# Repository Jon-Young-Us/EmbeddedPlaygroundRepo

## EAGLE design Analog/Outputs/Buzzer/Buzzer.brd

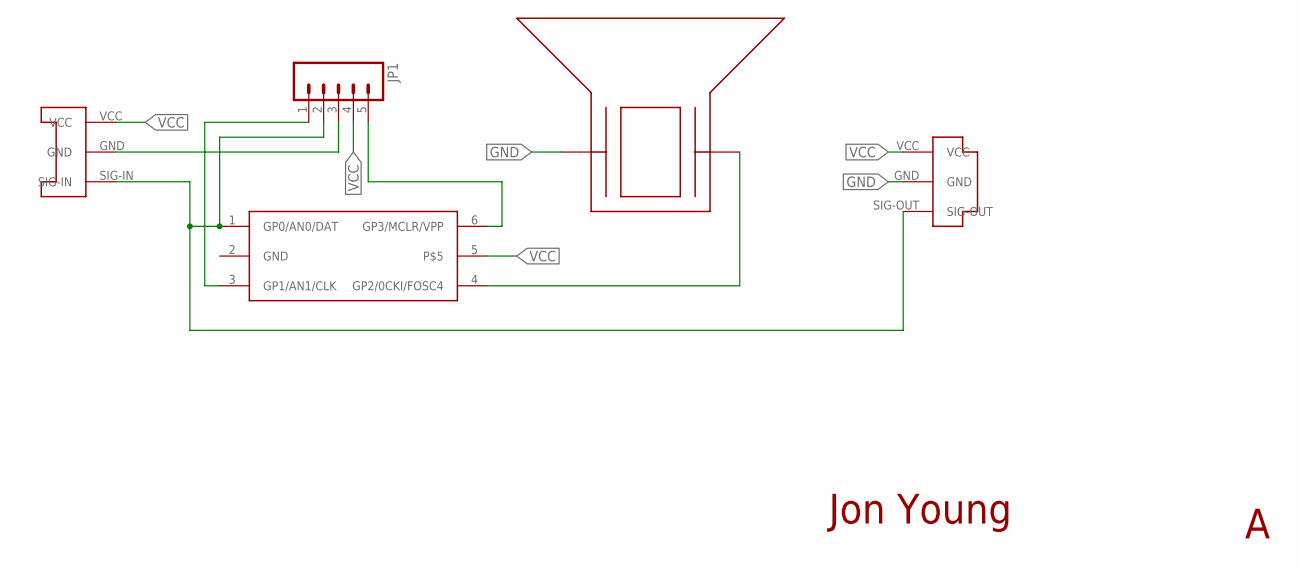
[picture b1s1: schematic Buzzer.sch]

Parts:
JP1: M051.27MM; 1X05-1.27MM
U$1: CONN-PLUG-3POS-3MM; PLUG-3POS-3MM-SMD
U$2: CONN-SOCKET-3POS-3MM; SOCKET-3POS-3MM-SMD
U$3: BUZZER; BUZZER-PKMCS0909E4000-R1
U$6: PIC10F2XXT-I/OT; SOT23-6

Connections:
GND: JP1.3, U$1.GND, U$2.GND, U$3.P$1, U$6.2 (GND)
unnamed: JP1.1, U$6.3 (GP1/AN1/CLK)
unnamed: JP1.2, U$1.SIG-OUT, U$2.SIG-IN, U$6.1 (GP0/AN0/DAT)
P$5: U$6.5
SIG-IN: U$3.P$2, U$6.4 (GP2/0CKI/FOSC4)
VCC: JP1.4, JP1.5, U$1.VCC, U$2.VCC, U$6.6 (GP3/MCLR/VPP)

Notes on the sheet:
Jon Young

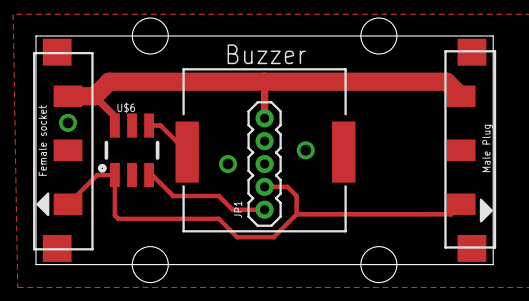
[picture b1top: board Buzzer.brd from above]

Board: 2 copper layers, 25.4 x 12.7 mm, 5 parts (0 on the bottom side), 5 nets.

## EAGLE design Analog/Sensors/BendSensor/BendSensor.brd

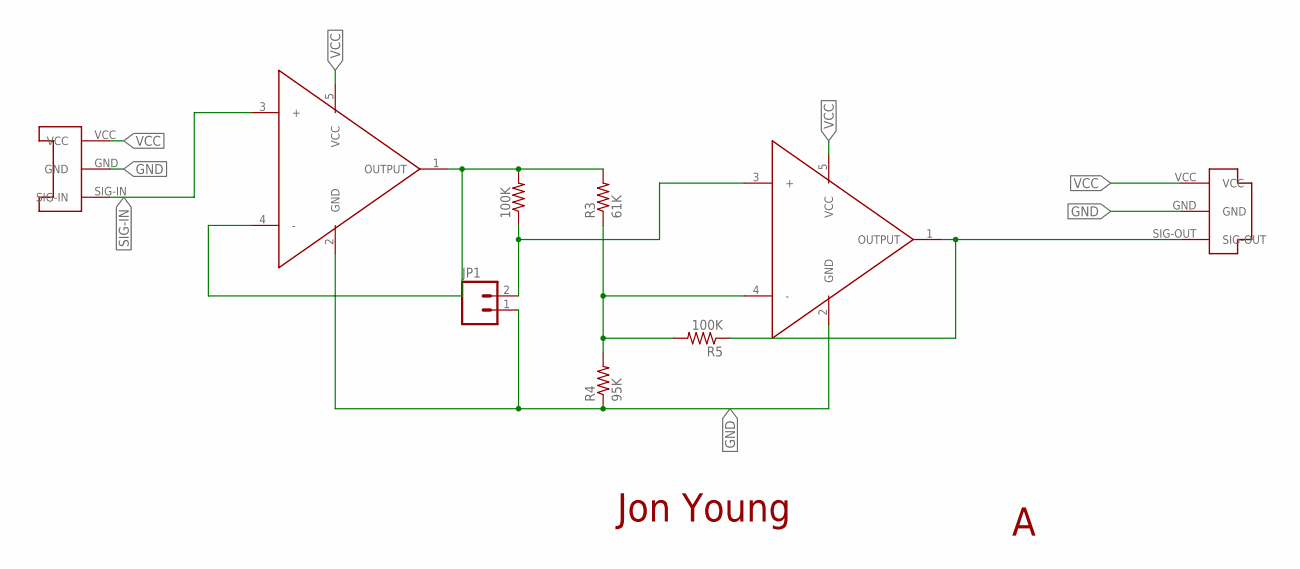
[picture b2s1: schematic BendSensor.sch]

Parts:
100K: RESISTOR0603; 0603-RES
JP1: M02PTH3; 1X02_LONGPADS
R3: 61K; 0603-RES
R4: 95K; 0603-RES
R5: 100K; 0603-RES
U$1: CONN-PLUG-3POS-3MM; PLUG-3POS-3MM-SMD
U$2: CONN-SOCKET-3POS-3MM; SOCKET-3POS-3MM-SMD
U$3, U$4: OPAMP-MCP6001SOT23-5; SOT23-5

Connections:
GND: JP1.1, R4.1, U$1.GND, U$2.GND, U$3.2 (GND), U$4.2 (GND)
unnamed: R5.1, U$1.SIG-OUT, U$4.1 (OUTPUT)
unnamed: R3.1, R4.2, R5.2, U$4.4 (-)
unnamed: 100K.2, R3.2, U$3.1 (OUTPUT), U$3.4 (-)
unnamed: 100K.1, JP1.2, U$4.3 (+)
SIG-IN: U$2.SIG-IN, U$3.3 (+)
VCC: U$1.VCC, U$2.VCC, U$3.5 (VCC), U$4.5 (VCC)

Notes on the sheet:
Jon Young

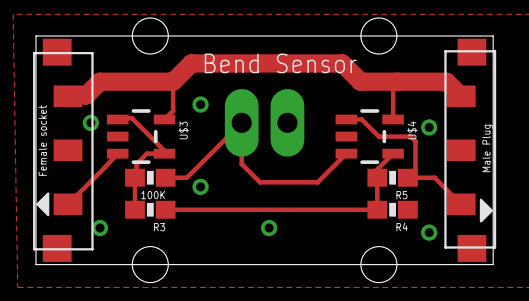
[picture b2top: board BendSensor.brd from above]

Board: 2 copper layers, 25.4 x 12.7 mm, 9 parts (0 on the bottom side), 7 nets.

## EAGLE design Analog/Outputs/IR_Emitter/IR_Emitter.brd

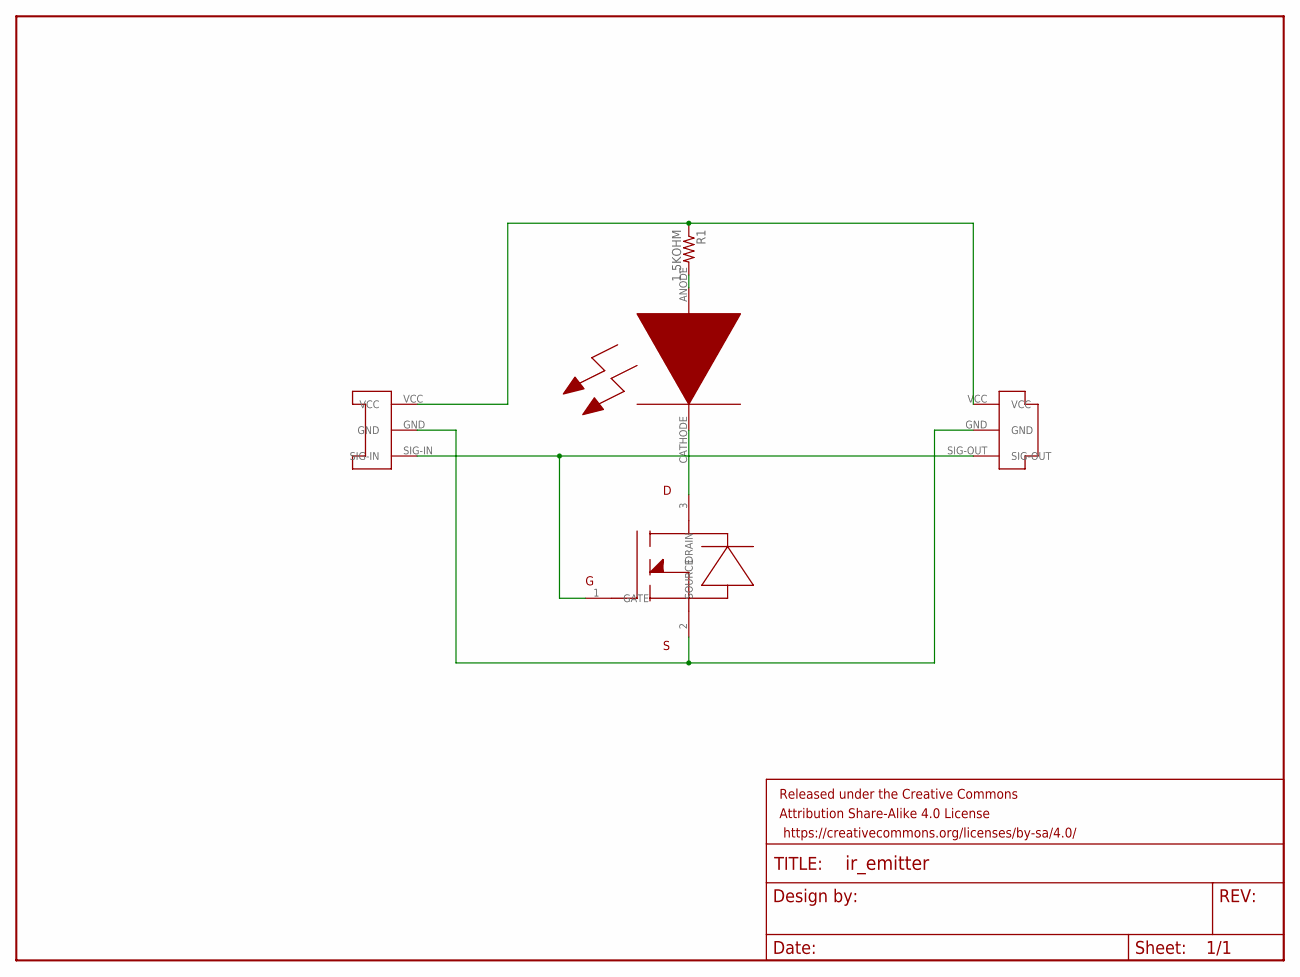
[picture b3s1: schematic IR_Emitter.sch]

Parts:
FRAME1: FRAME-LETTERNO_PACKAGE; DUMMY
R1: 1.5KOHM; 0603
U$1: CONN-PLUG-3POS-3MM; PLUG-3POS-3MM-SMD
U$2: CONN-SOCKET-3POS-3MM; SOCKET-3POS-3MM-SMD
U$3: MOSFET-N-CHAN; SOT23-3
U$4: IR-EMITTER-VSMB2943G; VEMD2020X01

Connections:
GND: U$1.GND, U$2.GND, U$3.2 (SOURCE)
unnamed: R1.2, U$4.ANODE
unnamed: U$3.3 (DRAIN), U$4.CATHODE
SIG: U$1.SIG-OUT, U$2.SIG-IN, U$3.1 (GATE)
VCC: R1.1, U$1.VCC, U$2.VCC

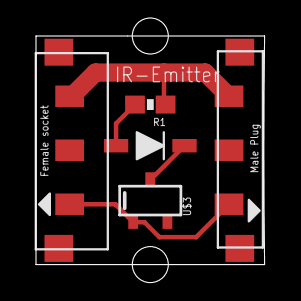
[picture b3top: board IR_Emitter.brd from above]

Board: 2 copper layers, 12.7 x 12.7 mm, 6 parts (0 on the bottom side), 5 nets.

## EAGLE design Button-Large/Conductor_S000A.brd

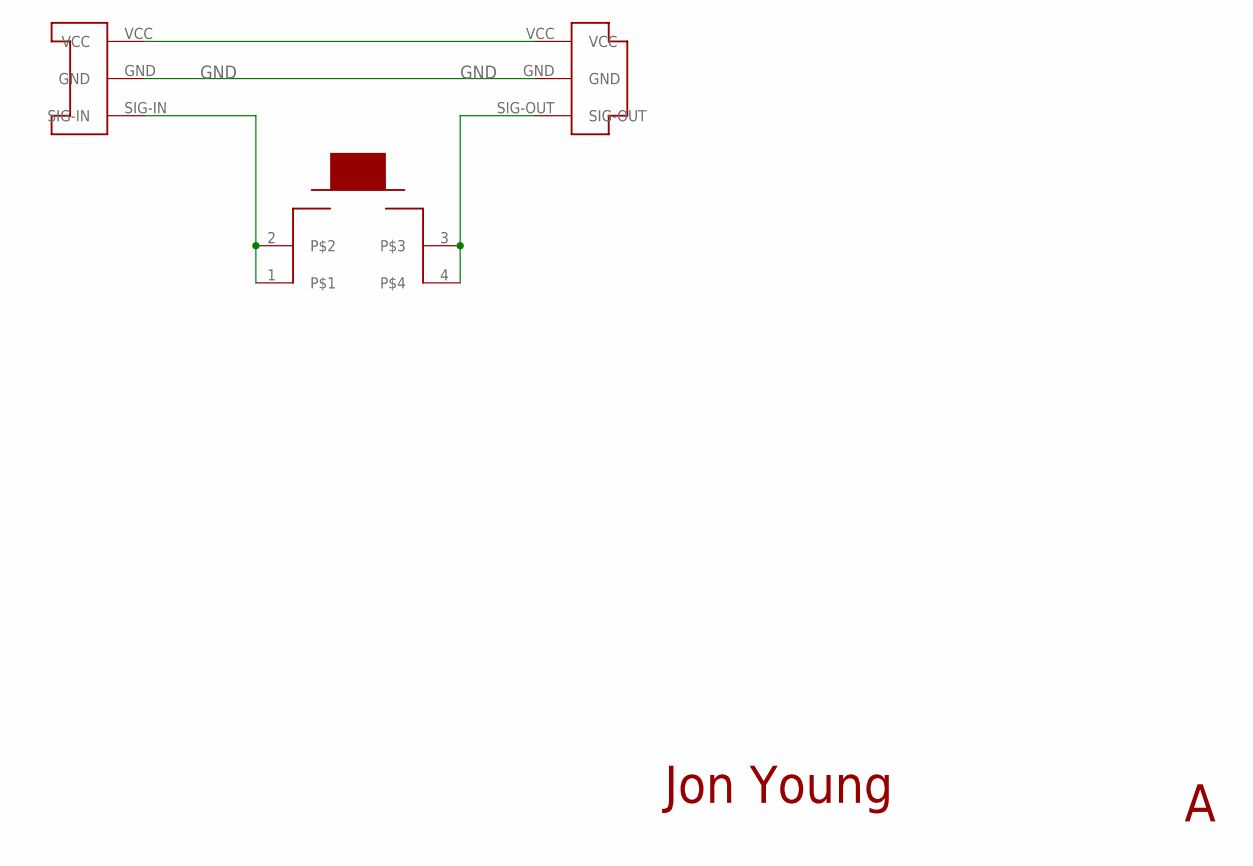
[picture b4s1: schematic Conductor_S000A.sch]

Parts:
U$1: CONN-PLUG-3POS-3MM; PLUG-3POS-3MM-SMD
U$2: CONN-SOCKET-3POS-3MM; SOCKET-3POS-3MM-SMD
U$3: PUSH_BUTTON; ESWITCH-TL3300CF260Q

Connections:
GND: U$1.GND, U$2.GND
unnamed: U$2.SIG-IN, U$3.1, U$3.2
unnamed: U$1.SIG-OUT, U$3.3, U$3.4
VCC: U$1.VCC, U$2.VCC

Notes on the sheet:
Jon Young

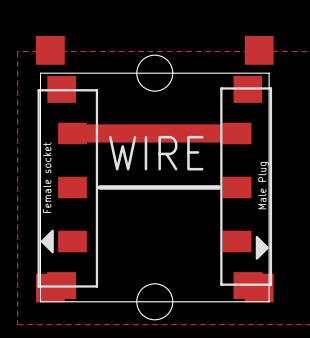
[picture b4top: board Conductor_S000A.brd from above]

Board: 2 copper layers, 12.7 x 12.7 mm, 3 parts (0 on the bottom side), 4 nets.

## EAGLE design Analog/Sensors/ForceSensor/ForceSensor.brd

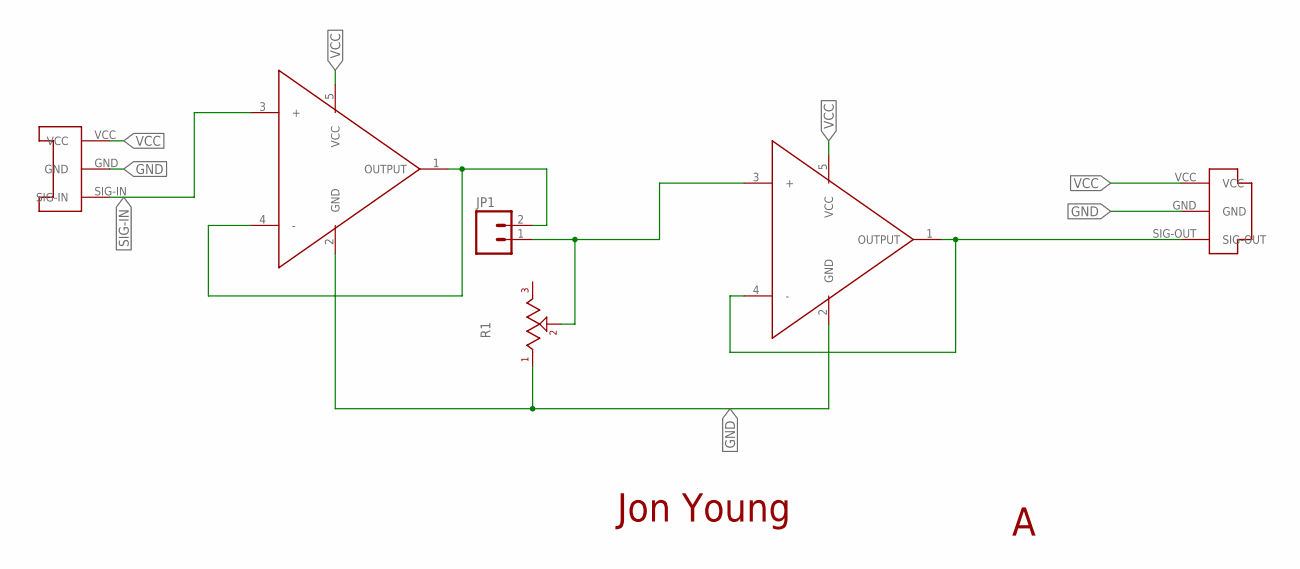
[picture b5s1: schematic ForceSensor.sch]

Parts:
JP1: M02PTH3; 1X02_LONGPADS
R1: POT-TRIM-SMD-BOURNS-3314J-1; POT-TRIM-SMD-BOURNS-3314
U$1: CONN-PLUG-3POS-3MM; PLUG-3POS-3MM-SMD
U$2: CONN-SOCKET-3POS-3MM; SOCKET-3POS-3MM-SMD
U$3, U$4: OPAMP-MCP6001SOT23-5; SOT23-5

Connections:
GND: R1.3 (1), U$1.GND, U$2.GND, U$3.2 (GND), U$4.2 (GND)
unnamed: U$1.SIG-OUT, U$4.1 (OUTPUT), U$4.4 (-)
unnamed: JP1.2, U$3.1 (OUTPUT), U$3.4 (-)
unnamed: JP1.1, R1.2, U$4.3 (+)
SIG-IN: U$2.SIG-IN, U$3.3 (+)
VCC: U$1.VCC, U$2.VCC, U$3.5 (VCC), U$4.5 (VCC)

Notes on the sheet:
Jon Young

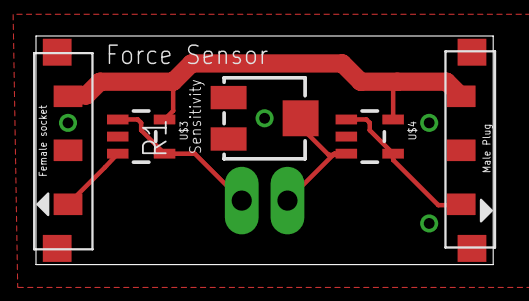
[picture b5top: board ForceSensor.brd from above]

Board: 2 copper layers, 25.4 x 12.7 mm, 6 parts (0 on the bottom side), 6 nets.

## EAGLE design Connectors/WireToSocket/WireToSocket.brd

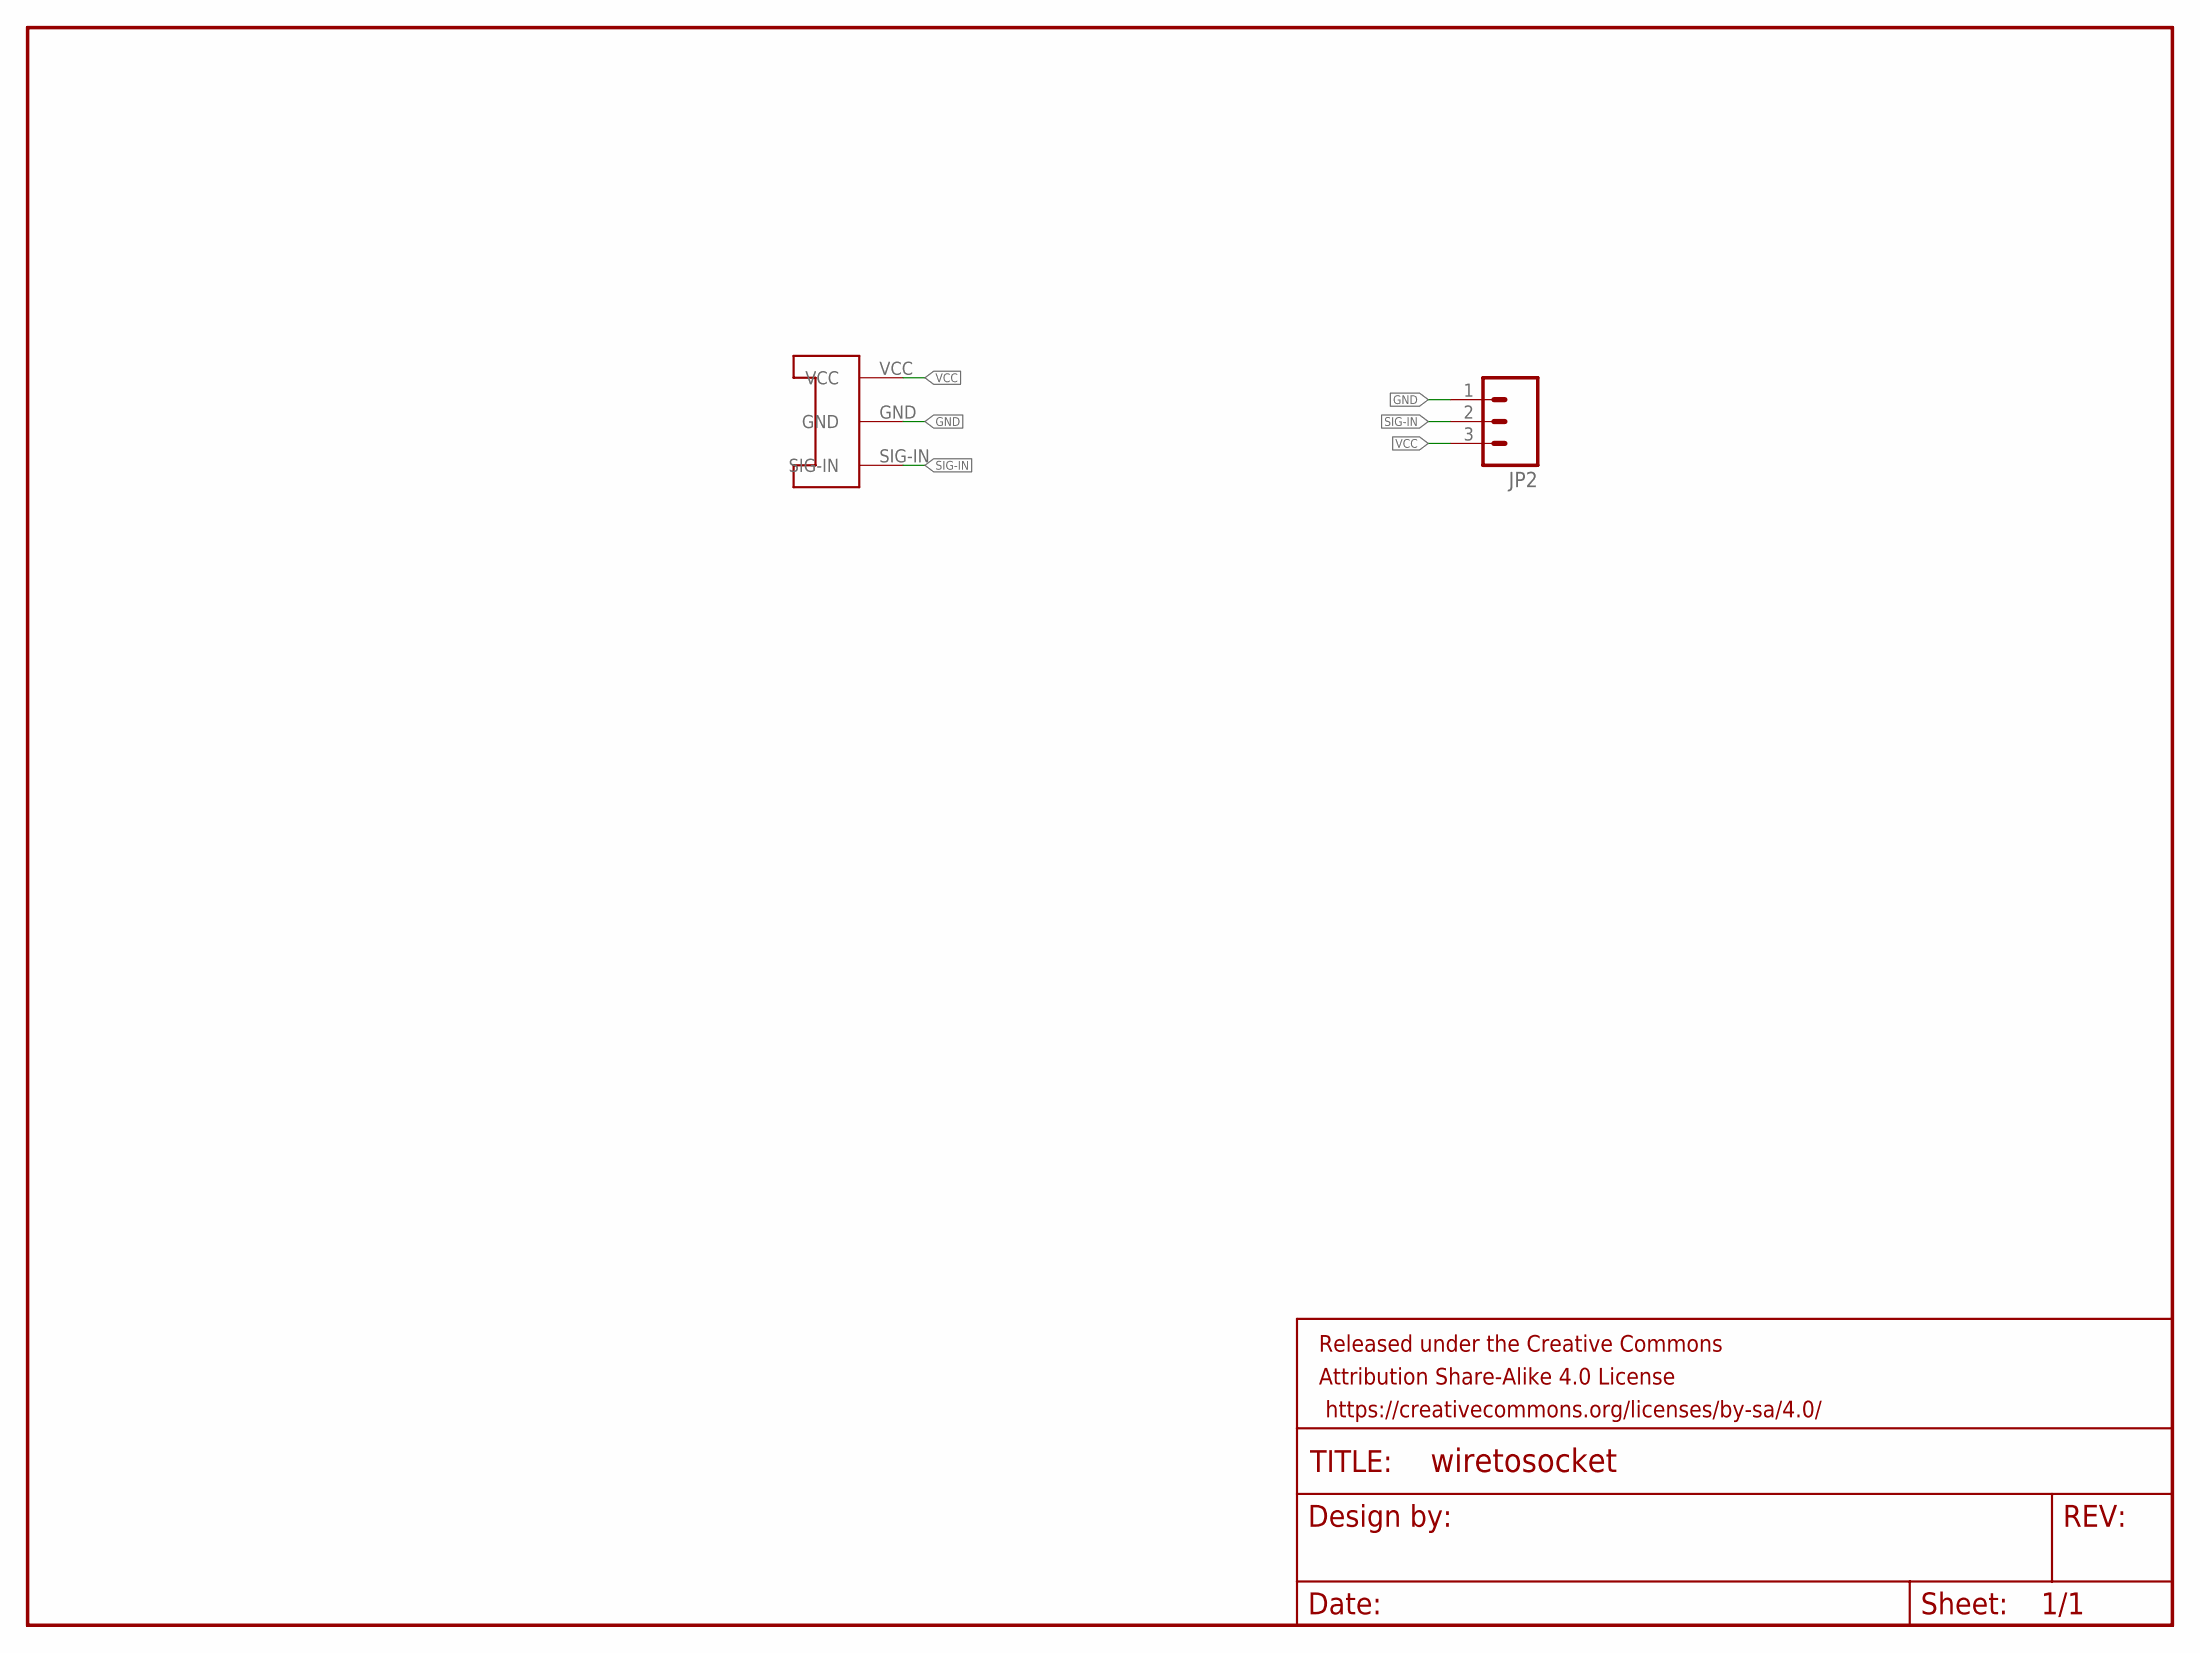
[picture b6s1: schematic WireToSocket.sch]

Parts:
FRAME1: FRAME-LETTERNO_PACKAGE; DUMMY
JP2: M03SMD; 1X03-1MM-RA
U$1: CONN-SOCKET-3POS-3MM; SOCKET-3POS-3MM-SMD

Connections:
GND: JP2.1, U$1.GND
SIG-IN: JP2.2, U$1.SIG-IN
VCC: JP2.3, U$1.VCC

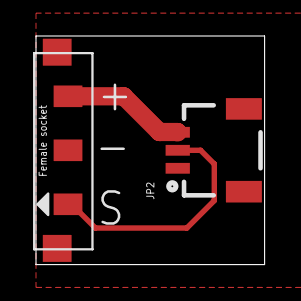
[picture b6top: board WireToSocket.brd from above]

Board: 2 copper layers, 12.7 x 12.7 mm, 3 parts (0 on the bottom side), 3 nets.

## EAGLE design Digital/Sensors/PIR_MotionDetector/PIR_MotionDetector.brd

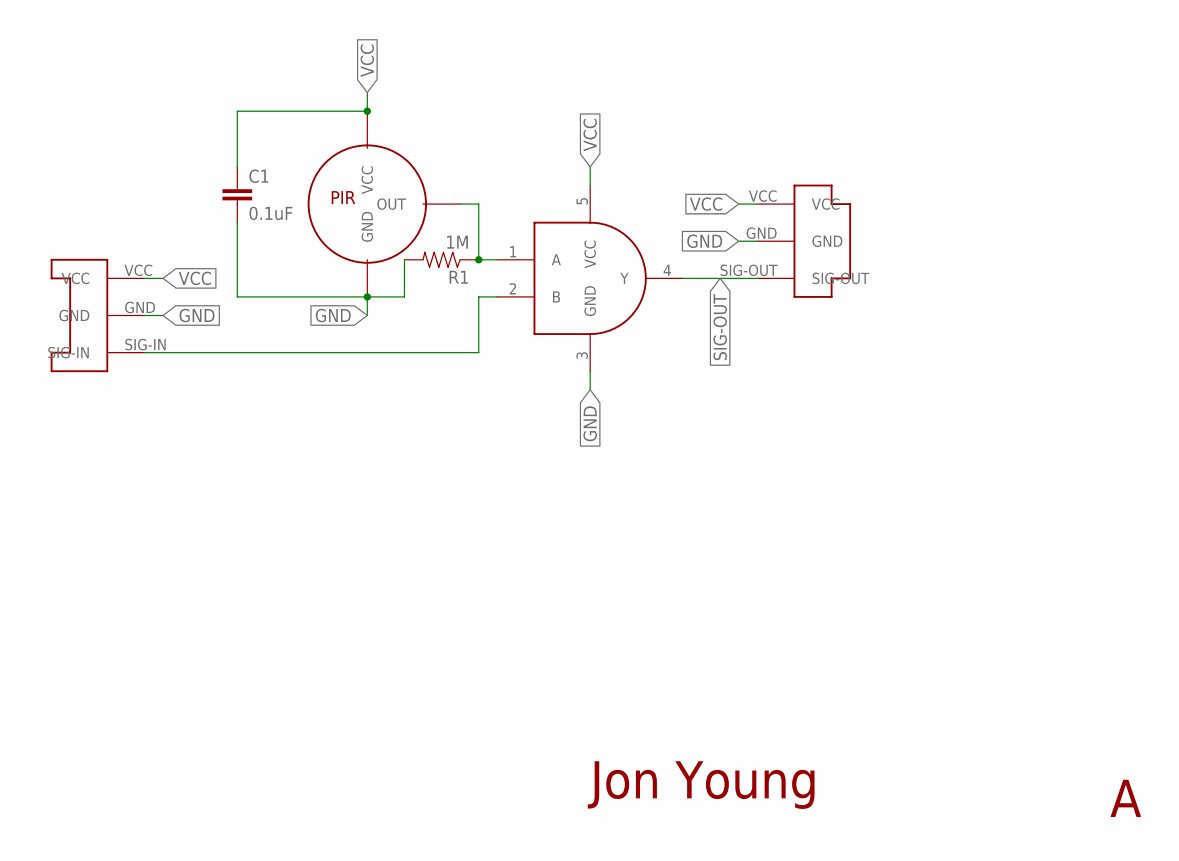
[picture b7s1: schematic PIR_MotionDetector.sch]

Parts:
C1: 0.1uF; 0603-CAP
R1: 1M; 0603-RES
U$1: CONN-PLUG-3POS-3MM; PLUG-3POS-3MM-SMD
U$2: CONN-SOCKET-3POS-3MM; SOCKET-3POS-3MM-SMD
U$3: PIR-PANASONIC-WL; TO-5-3PIN
U$4: AND-NC7SZ08; SC70

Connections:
GND: C1.2, R1.2, U$1.GND, U$2.GND, U$3.GND, U$4.3 (GND)
unnamed: R1.1, U$3.OUT, U$4.1 (A)
SIG-IN: U$2.SIG-IN, U$4.2 (B)
SIG-OUT: U$1.SIG-OUT, U$4.4 (Y)
VCC: C1.1, U$1.VCC, U$2.VCC, U$3.VCC, U$4.5 (VCC)

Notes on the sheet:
Jon Young

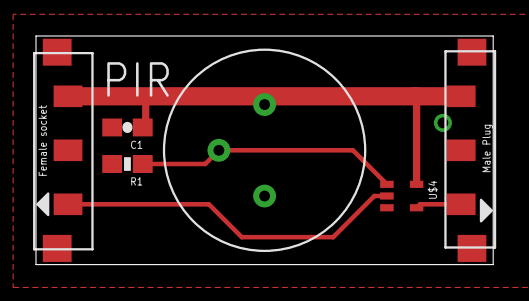
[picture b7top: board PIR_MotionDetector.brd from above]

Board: 2 copper layers, 25.4 x 12.7 mm, 6 parts (0 on the bottom side), 5 nets.

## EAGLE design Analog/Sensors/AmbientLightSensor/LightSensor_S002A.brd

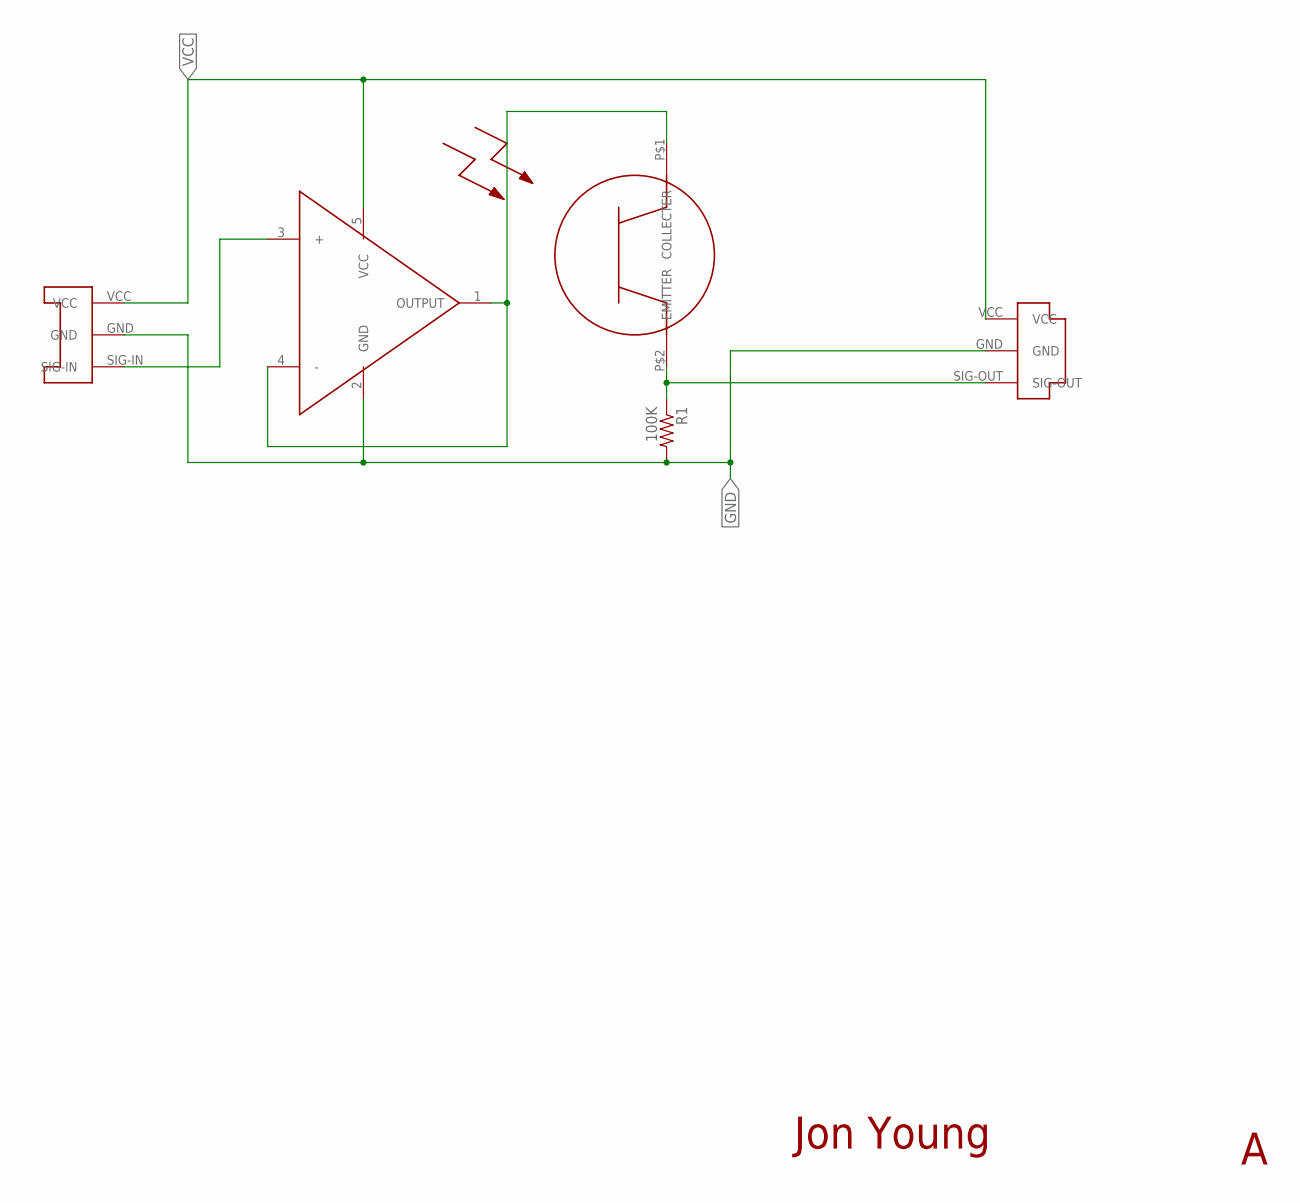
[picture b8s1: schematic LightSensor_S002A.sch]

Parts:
R1: 100K; 0603-RES
U$1: CONN-PLUG-3POS-3MM; PLUG-3POS-3MM-SMD
U$2: CONN-SOCKET-3POS-3MM; SOCKET-3POS-3MM-SMD
U$3: OPAMP-MCP6001SC70-5; SC70
U$4: AMBIENT-LIGHT-SENSOR-DIODE; AMBIENT-LIGHT-SENSOR-PT19

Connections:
GND: R1.2, U$1.GND, U$2.GND, U$3.2 (GND)
unnamed: R1.1, U$1.SIG-OUT, U$4.P$2 (EMITTER)
unnamed: U$3.1 (OUTPUT), U$3.4 (-), U$4.P$1 (COLLECTER)
SIG-IN: U$2.SIG-IN, U$3.3 (+)
VCC: U$1.VCC, U$2.VCC, U$3.5 (VCC)

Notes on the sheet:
Jon Young

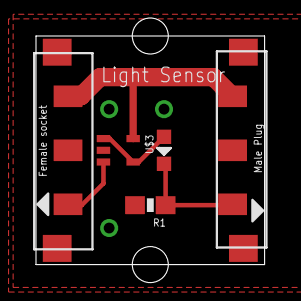
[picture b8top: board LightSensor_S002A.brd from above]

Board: 2 copper layers, 12.7 x 12.7 mm, 5 parts (0 on the bottom side), 5 nets.

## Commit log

2016-03-27 :octocat: Added .gitattributes & .gitignore files
2016-03-27 Initial Commit
    Initial state of hardware design files

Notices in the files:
parts and their libraries:
SparkFun-Connectors: Licensing: Creative Commons ShareAlike 4.0 International - https://creativecommons.org/licenses/by-sa/4.0
SparkFun-Aesthetics: Released under the Creative Commons Attribution Share-Alike 4.0 License
SparkFun-Aesthetics: https://creativecommons.org/licenses/by-sa/4.0
